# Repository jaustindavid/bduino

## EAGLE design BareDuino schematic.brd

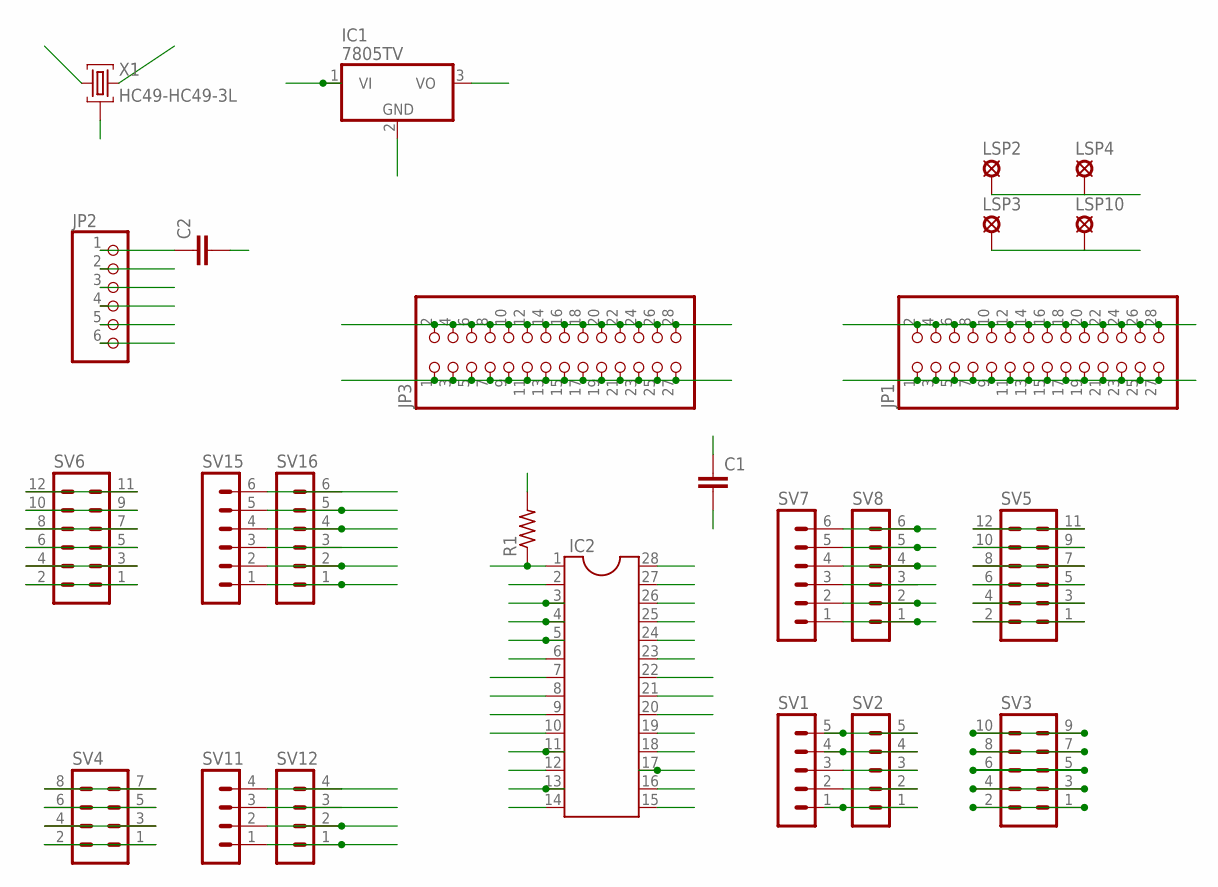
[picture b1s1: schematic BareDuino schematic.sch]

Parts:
C1, C2: C5/2.5; C5B2.5
IC1: 7805TV; TO220V
IC2: DIL28-3
JP1, JP3: PINHD-2X14; 2X14
JP2: PINHD-1X6; 1X06
LSP2, LSP3: SE14
LSP4, LSP10: LSP10
R1: R-US_0204/5; 0204/5
SV1, SV2: MA05-1
SV3: MA05-2
SV4: MA04-2
SV5, SV6: MA06-2
SV7, SV8, SV15, SV16: MA06-1
SV11, SV12: MA04-1
X1: HC49-HC49-3L; HC49-3L

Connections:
CLK-9: IC2.9, X1.1
CLK-10: IC2.10, X1.3
DIP2: IC2.2, JP2.3, SV15.5, SV16.5
DIP3: IC2.3, JP2.2, SV15.4, SV16.4
DIP4: IC2.4, SV15.3, SV16.3
DIP5: IC2.5, SV15.2, SV16.2
DIP6: IC2.6, SV15.1, SV16.1
DIP11: IC2.11, SV11.4, SV12.4
DIP12: IC2.12, SV11.3, SV12.3
DIP13: IC2.13, SV11.2, SV12.2
DIP14: IC2.14, SV11.1, SV12.1
DIP15: IC2.15, SV1.1, SV2.1
DIP16: IC2.16, SV1.2, SV2.2
DIP17: IC2.17, SV1.3, SV2.3
DIP18: IC2.18, SV1.4, SV2.4
DIP19: IC2.19, SV1.5, SV2.5
DIP23: IC2.23, SV7.1, SV8.1
DIP24: IC2.24, SV7.2, SV8.2
DIP25: IC2.25, SV7.3, SV8.3
DIP26: IC2.26, SV7.4, SV8.4
DIP27: IC2.27, SV7.5, SV8.5
DIP28: IC2.28, SV7.6, SV8.6
GND: C1.1, IC1.2 (GND), IC2.8, IC2.22, JP1.2, JP1.4, JP1.6, JP1.8, JP1.10, JP1.12, JP1.14, JP1.16, JP1.18, JP1.20, JP1.22, JP1.24, JP1.26, JP1.28, JP2.5, JP2.6, JP3.1, JP3.3, JP3.5, JP3.7, JP3.9, JP3.11, JP3.13, JP3.15, JP3.17, JP3.19, JP3.21, JP3.23, JP3.25, JP3.27, LSP3.MP, LSP10.MP, X1.2
unnamed: SV5.11, SV5.12
unnamed: SV5.9, SV5.10
unnamed: SV5.7, SV5.8
unnamed: SV5.5, SV5.6
unnamed: SV5.3, SV5.4
unnamed: SV5.1, SV5.2
unnamed: SV4.7, SV4.8
unnamed: SV4.5, SV4.6
unnamed: SV4.3, SV4.4
unnamed: SV4.1, SV4.2
unnamed: SV6.11, SV6.12
unnamed: SV3.5, SV3.6
unnamed: SV3.7, SV3.8
unnamed: SV3.9, SV3.10
unnamed: SV3.3, SV3.4
unnamed: SV3.1, SV3.2
unnamed: SV6.9, SV6.10
unnamed: SV6.7, SV6.8
unnamed: SV6.5, SV6.6
unnamed: SV6.3, SV6.4
unnamed: C2.1, JP2.1
unnamed: SV6.1, SV6.2
RST: C2.2, IC2.1, R1.1, SV15.6, SV16.6
VCC: C1.2, IC1.3 (VO), IC2.7, IC2.20, IC2.21, JP1.1, JP1.3, JP1.5, JP1.7, JP1.9, JP1.11, JP1.13, JP1.15, JP1.17, JP1.19, JP1.21, JP1.23, JP1.25, JP1.27, JP2.4, JP3.2, JP3.4, JP3.6, JP3.8, JP3.10, JP3.12, JP3.14, JP3.16, JP3.18, JP3.20, JP3.22, JP3.24, JP3.26, JP3.28, R1.2
VIN: IC1.1 (VI), LSP2.MP, LSP4.MP

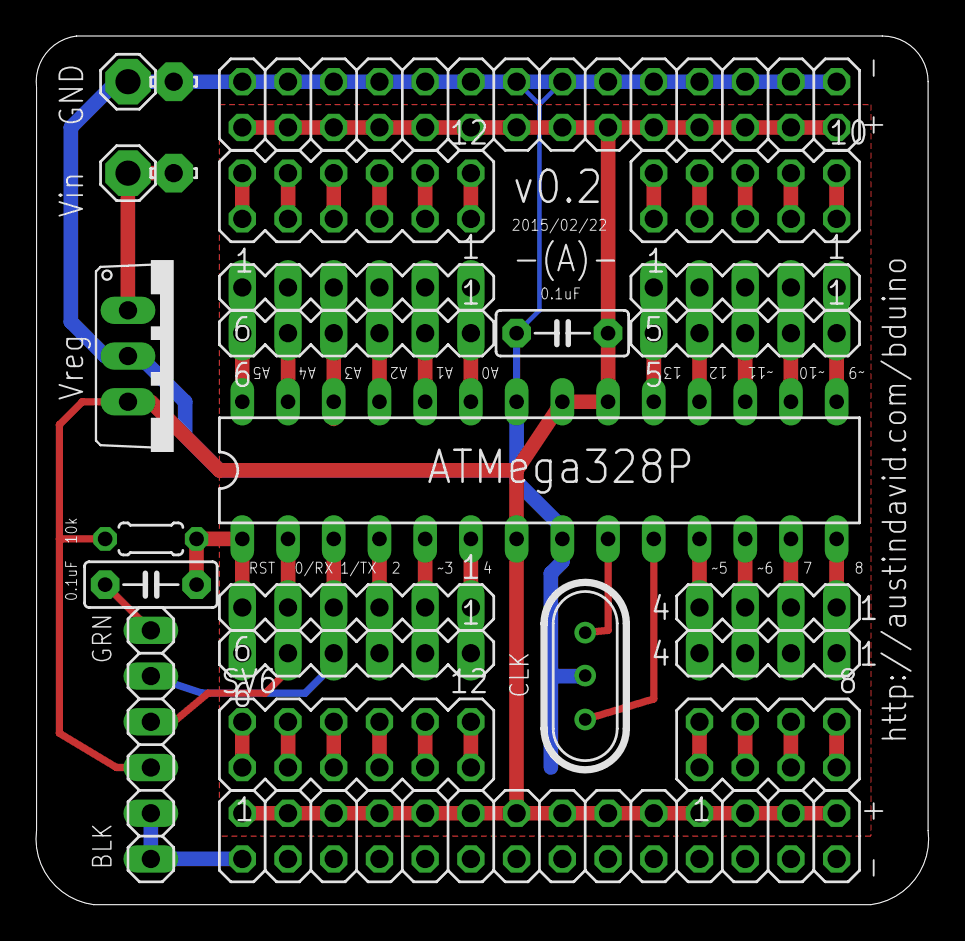
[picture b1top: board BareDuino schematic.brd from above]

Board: 2 copper layers, 49.6 x 48.3 mm, 25 parts (0 on the bottom side), 48 nets.

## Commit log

2015-08-23 bduino / bareduino intro
    a lightest-useful breakout for ATmega328P. Includes power, crystal,
    filtering cap.
2015-08-23 cleanup for fab
    mostly font changes
2016-02-23 update! cleanup + servos + FTDI
    fixes missing traces, realigns the breakout pads to make *all* of them
    servo-friendly, adds an FTDI header, and adds labels on (most) pins
